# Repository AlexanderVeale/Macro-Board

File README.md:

# Macro-Board
DIY macro keyboard project

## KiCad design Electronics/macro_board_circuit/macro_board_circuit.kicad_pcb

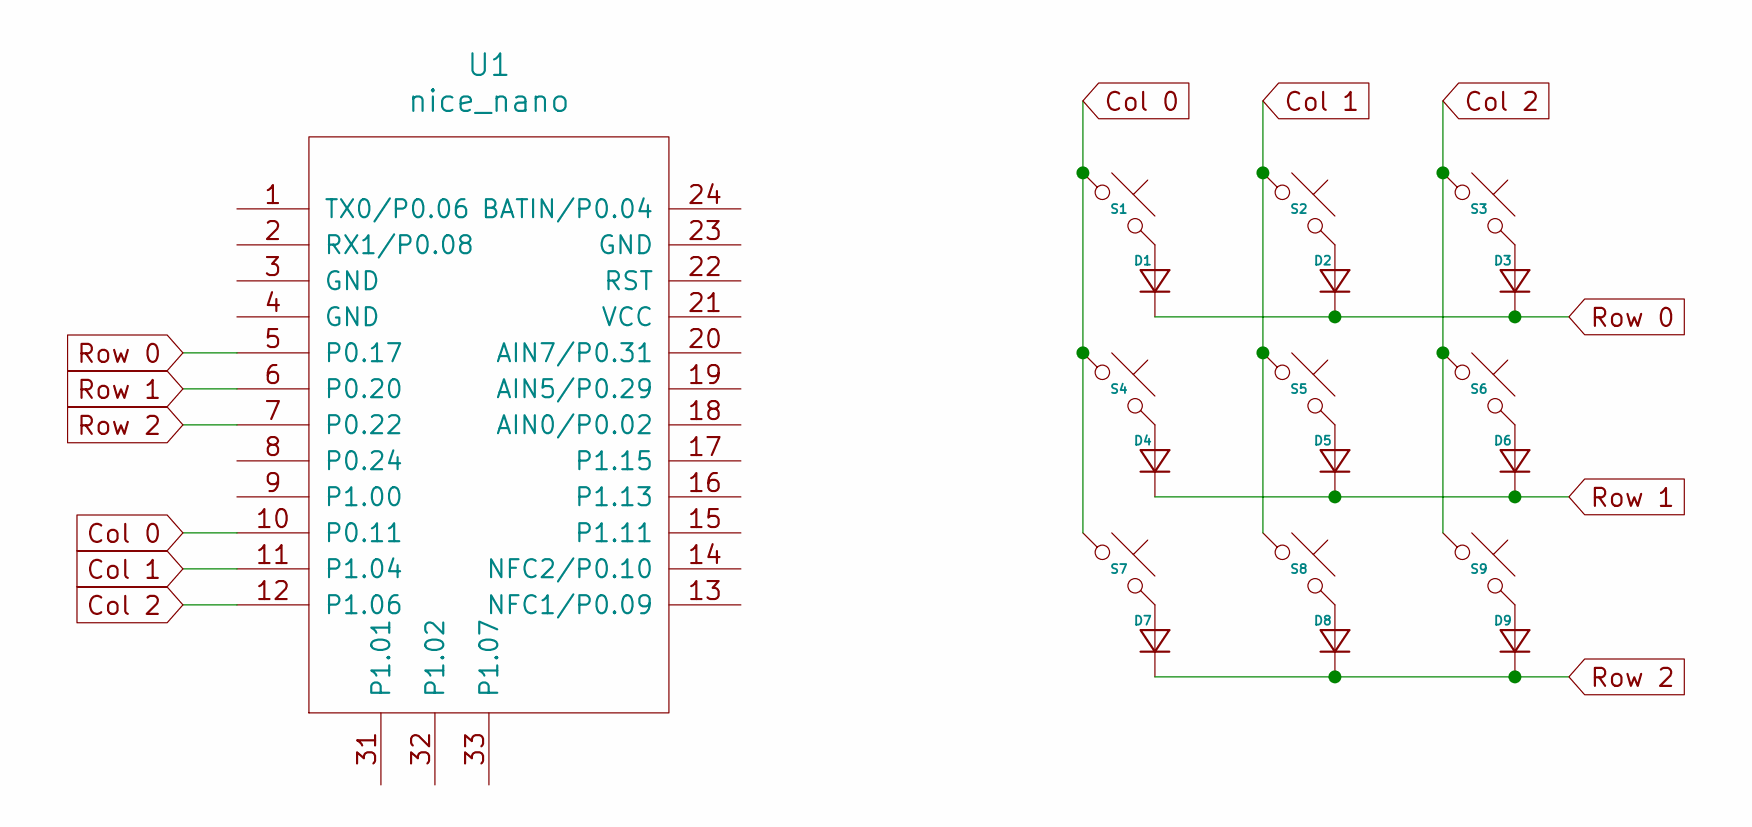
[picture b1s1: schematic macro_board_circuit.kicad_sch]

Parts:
D1, D2, D3, D4, D5, D6, D7, D8, D9: D_DO-35_SOD27_P7.62mm_Horizontal
S1, S2, S3, S4, S5, S6, S7, S8, S9: MX_PCB_1.00u
U1: nice_nano

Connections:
Col 0: S1.1, S4.1, S7.1, U1.10 (P0.11)
Col 1: S2.1, S5.1, S8.1, U1.11 (P1.04)
Col 2: S3.1, S6.1, S9.1, U1.12 (P1.06)
unnamed: D1.2 (A), S1.2
unnamed: D2.2 (A), S2.2
unnamed: D3.2 (A), S3.2
unnamed: D4.2 (A), S4.2
unnamed: D5.2 (A), S5.2
unnamed: D6.2 (A), S6.2
unnamed: D7.2 (A), S7.2
unnamed: D8.2 (A), S8.2
unnamed: D9.2 (A), S9.2
Row 0: D1.1 (K), D2.1 (K), D3.1 (K), U1.5 (P0.17)
Row 1: D4.1 (K), D5.1 (K), D6.1 (K), U1.6 (P0.20)
Row 2: D7.1 (K), D8.1 (K), D9.1 (K), U1.7 (P0.22)

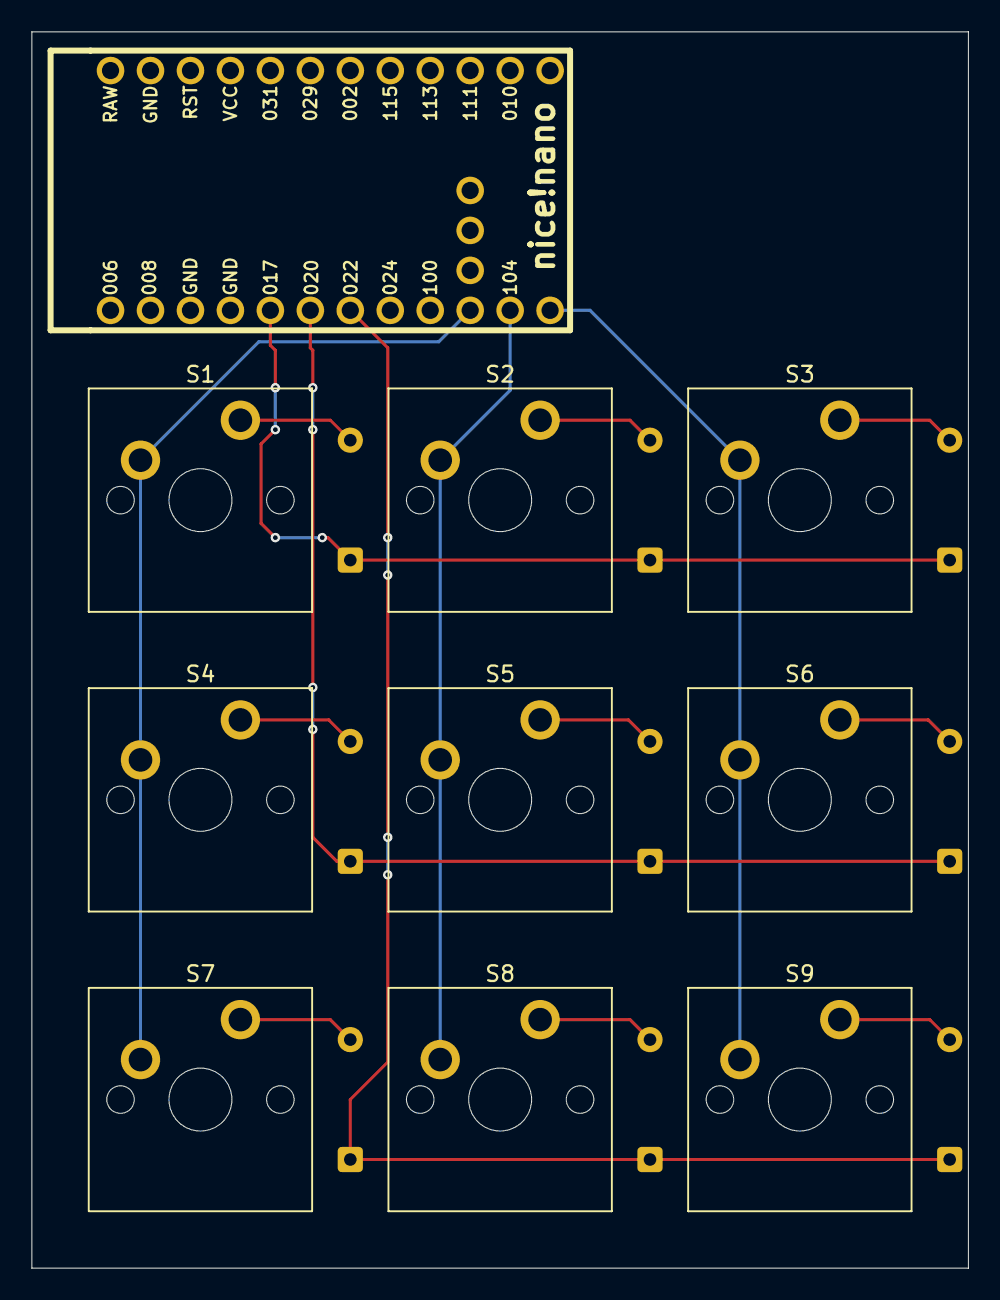
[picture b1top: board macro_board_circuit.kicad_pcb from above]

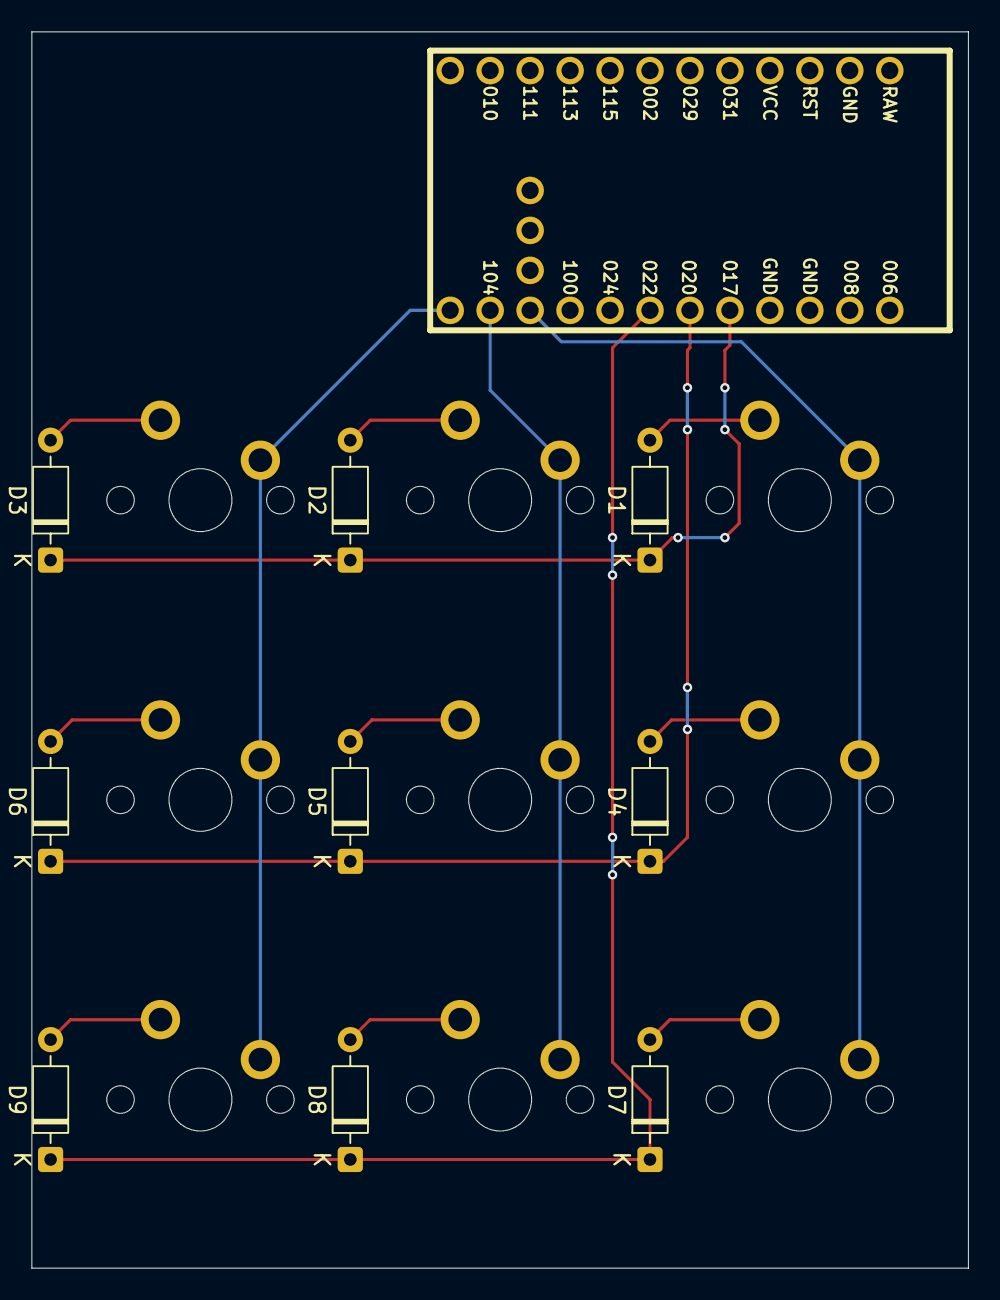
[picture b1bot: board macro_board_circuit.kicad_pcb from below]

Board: 2 copper layers, 59.5 x 78.6 mm, 19 parts (9 on the bottom side), 15 nets.

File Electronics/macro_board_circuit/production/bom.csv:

Designator,Footprint,Quantity,Value,LCSC Part #
"D1, D2, D3, D4, D5, D6, D7, D8, D9",D_DO-35_SOD27_P7.62mm_Horizontal,9,~,
"S1, S2, S3, S4, S5, S6, S7, S8, S9",MX_PCB_1.00u,9,~,
U1,nice_nano,1,nice_nano,

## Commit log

2026-01-08 Created circuit file
    In KiCad
2026-01-08 First circuit design
    Only controller + switches/diodes so far
2026-01-08 First PCB design + prod. export
2026-01-14 Added EC11 + fill volume
    Added the EC11 encoder/switch and a copper fill volume to the PCB.
2026-01-14 Created assembly for solid components
    Created a creo assembly for the shell and other solid components of the macro board.
2026-01-14 Case first draft
    Imported the PCB .step into creo, created first draft of the macro boards case.
2026-01-14 New PCB export
2026-01-14 Updated shell part
    Added holes for heat inserts and added a divot for aligning the top plate.
2026-01-18 Created Lid Part
    Created a lid to screw onto the shell with holes for the keycaps and screws
